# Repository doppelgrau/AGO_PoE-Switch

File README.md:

# AGO_PoE-Switch

A simple ethernet switch, four ports with passive PoE, one without.
Input protected against reverse polarity and over voltage (>15V)

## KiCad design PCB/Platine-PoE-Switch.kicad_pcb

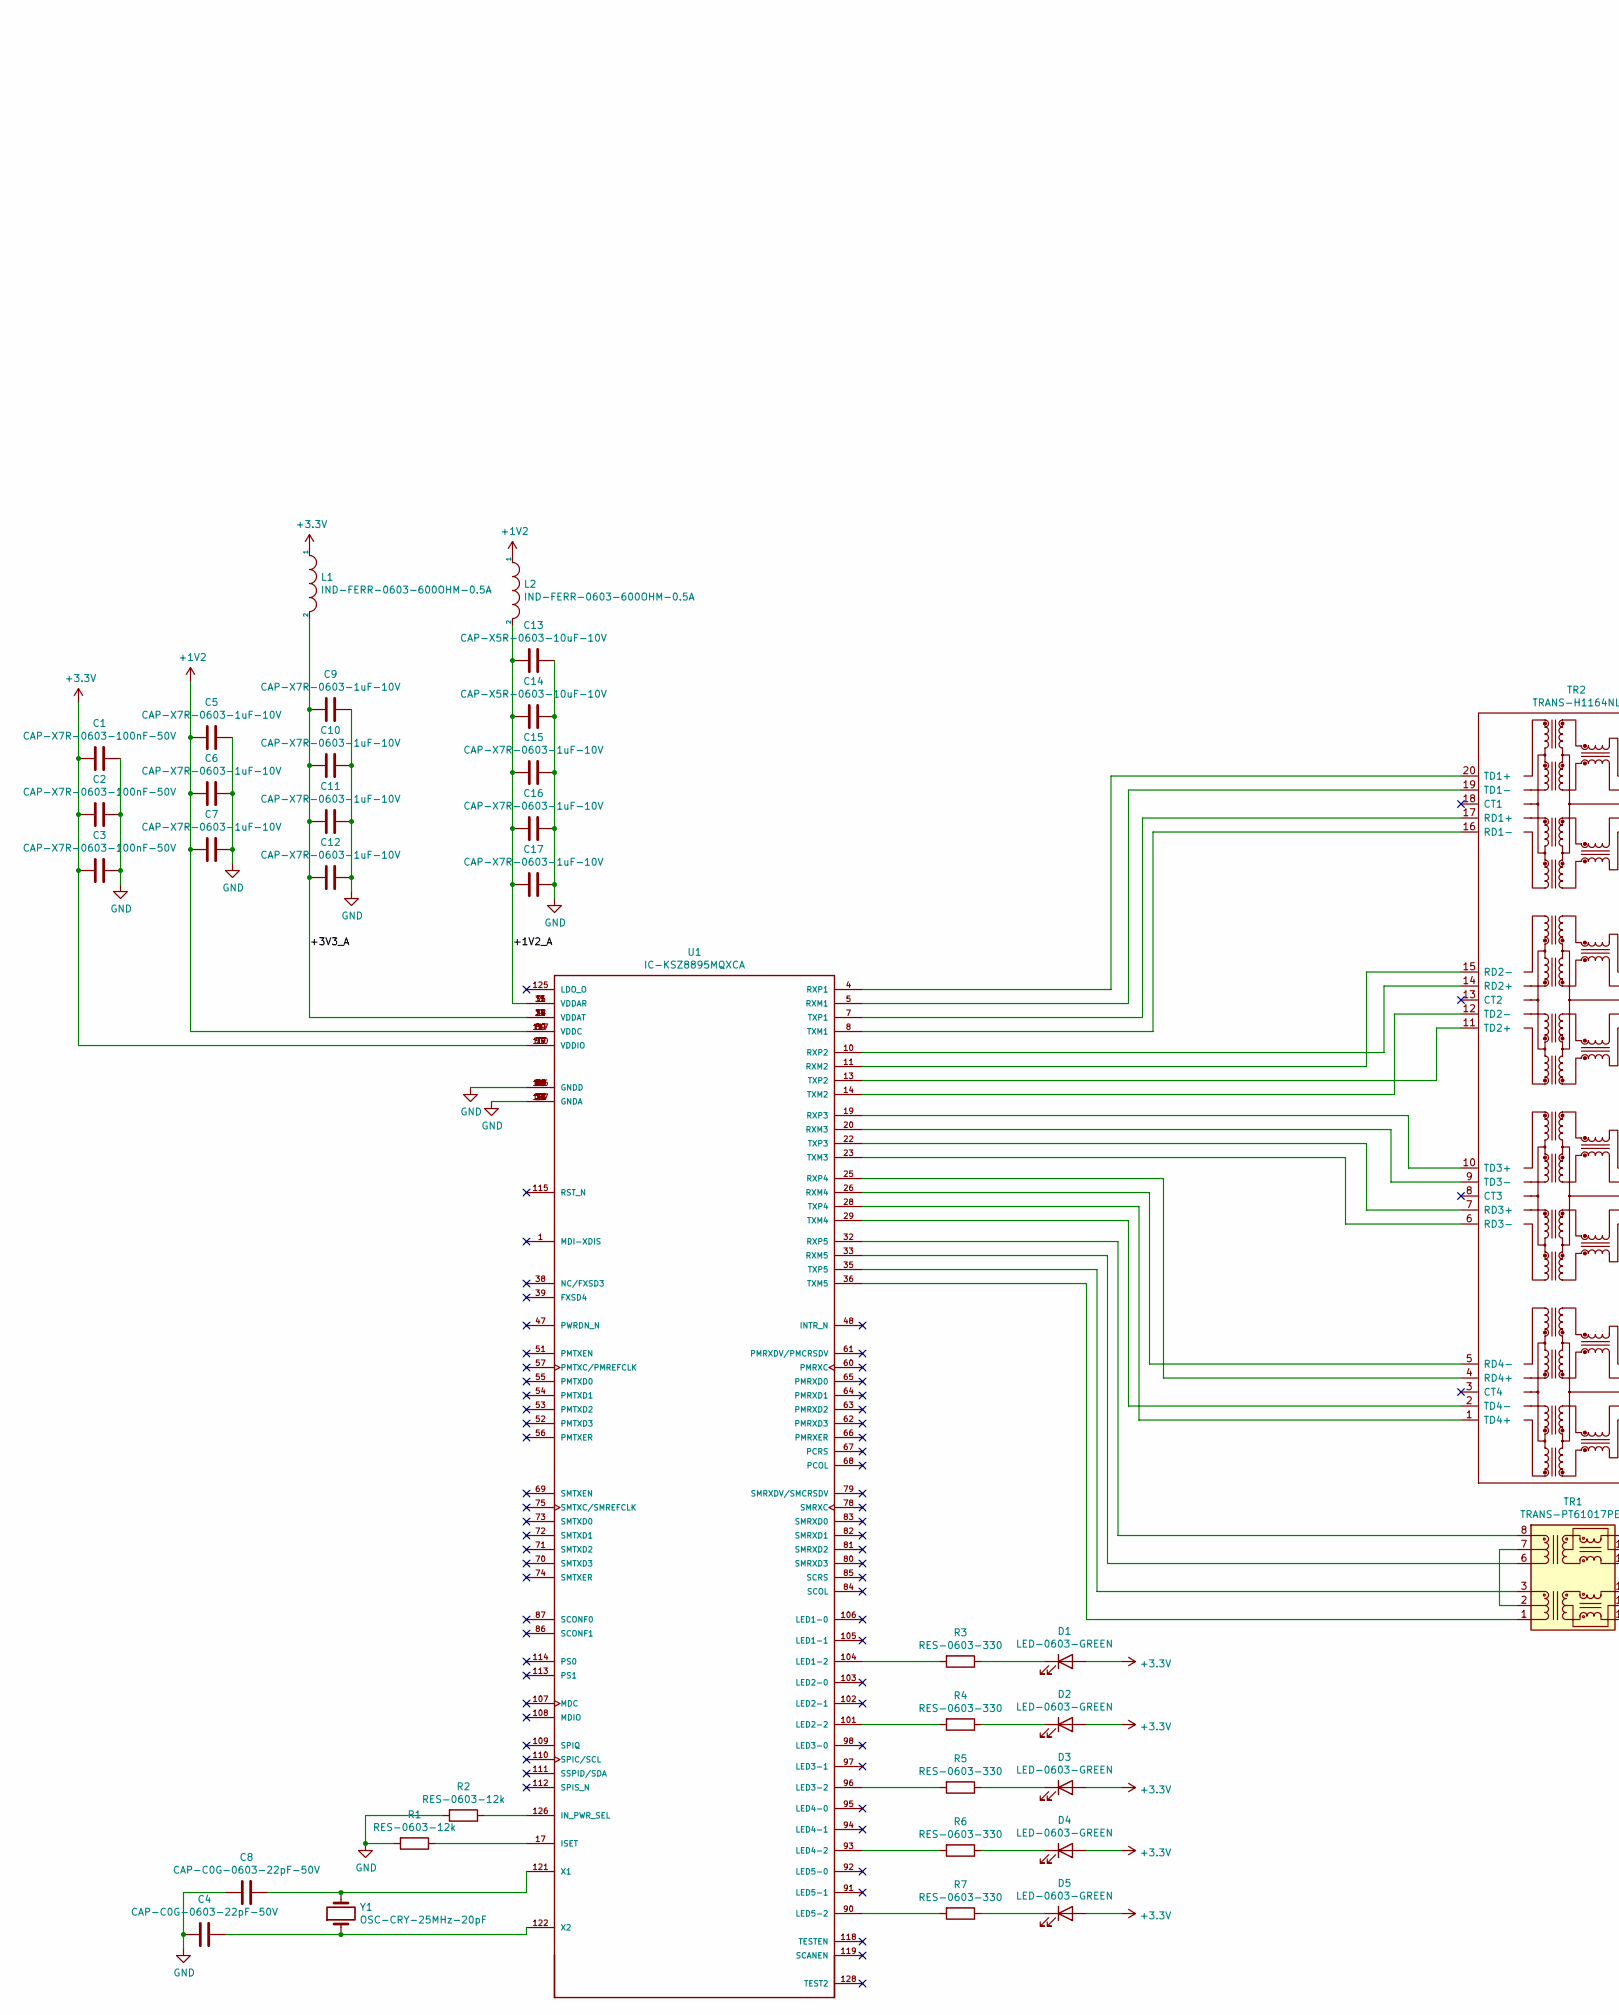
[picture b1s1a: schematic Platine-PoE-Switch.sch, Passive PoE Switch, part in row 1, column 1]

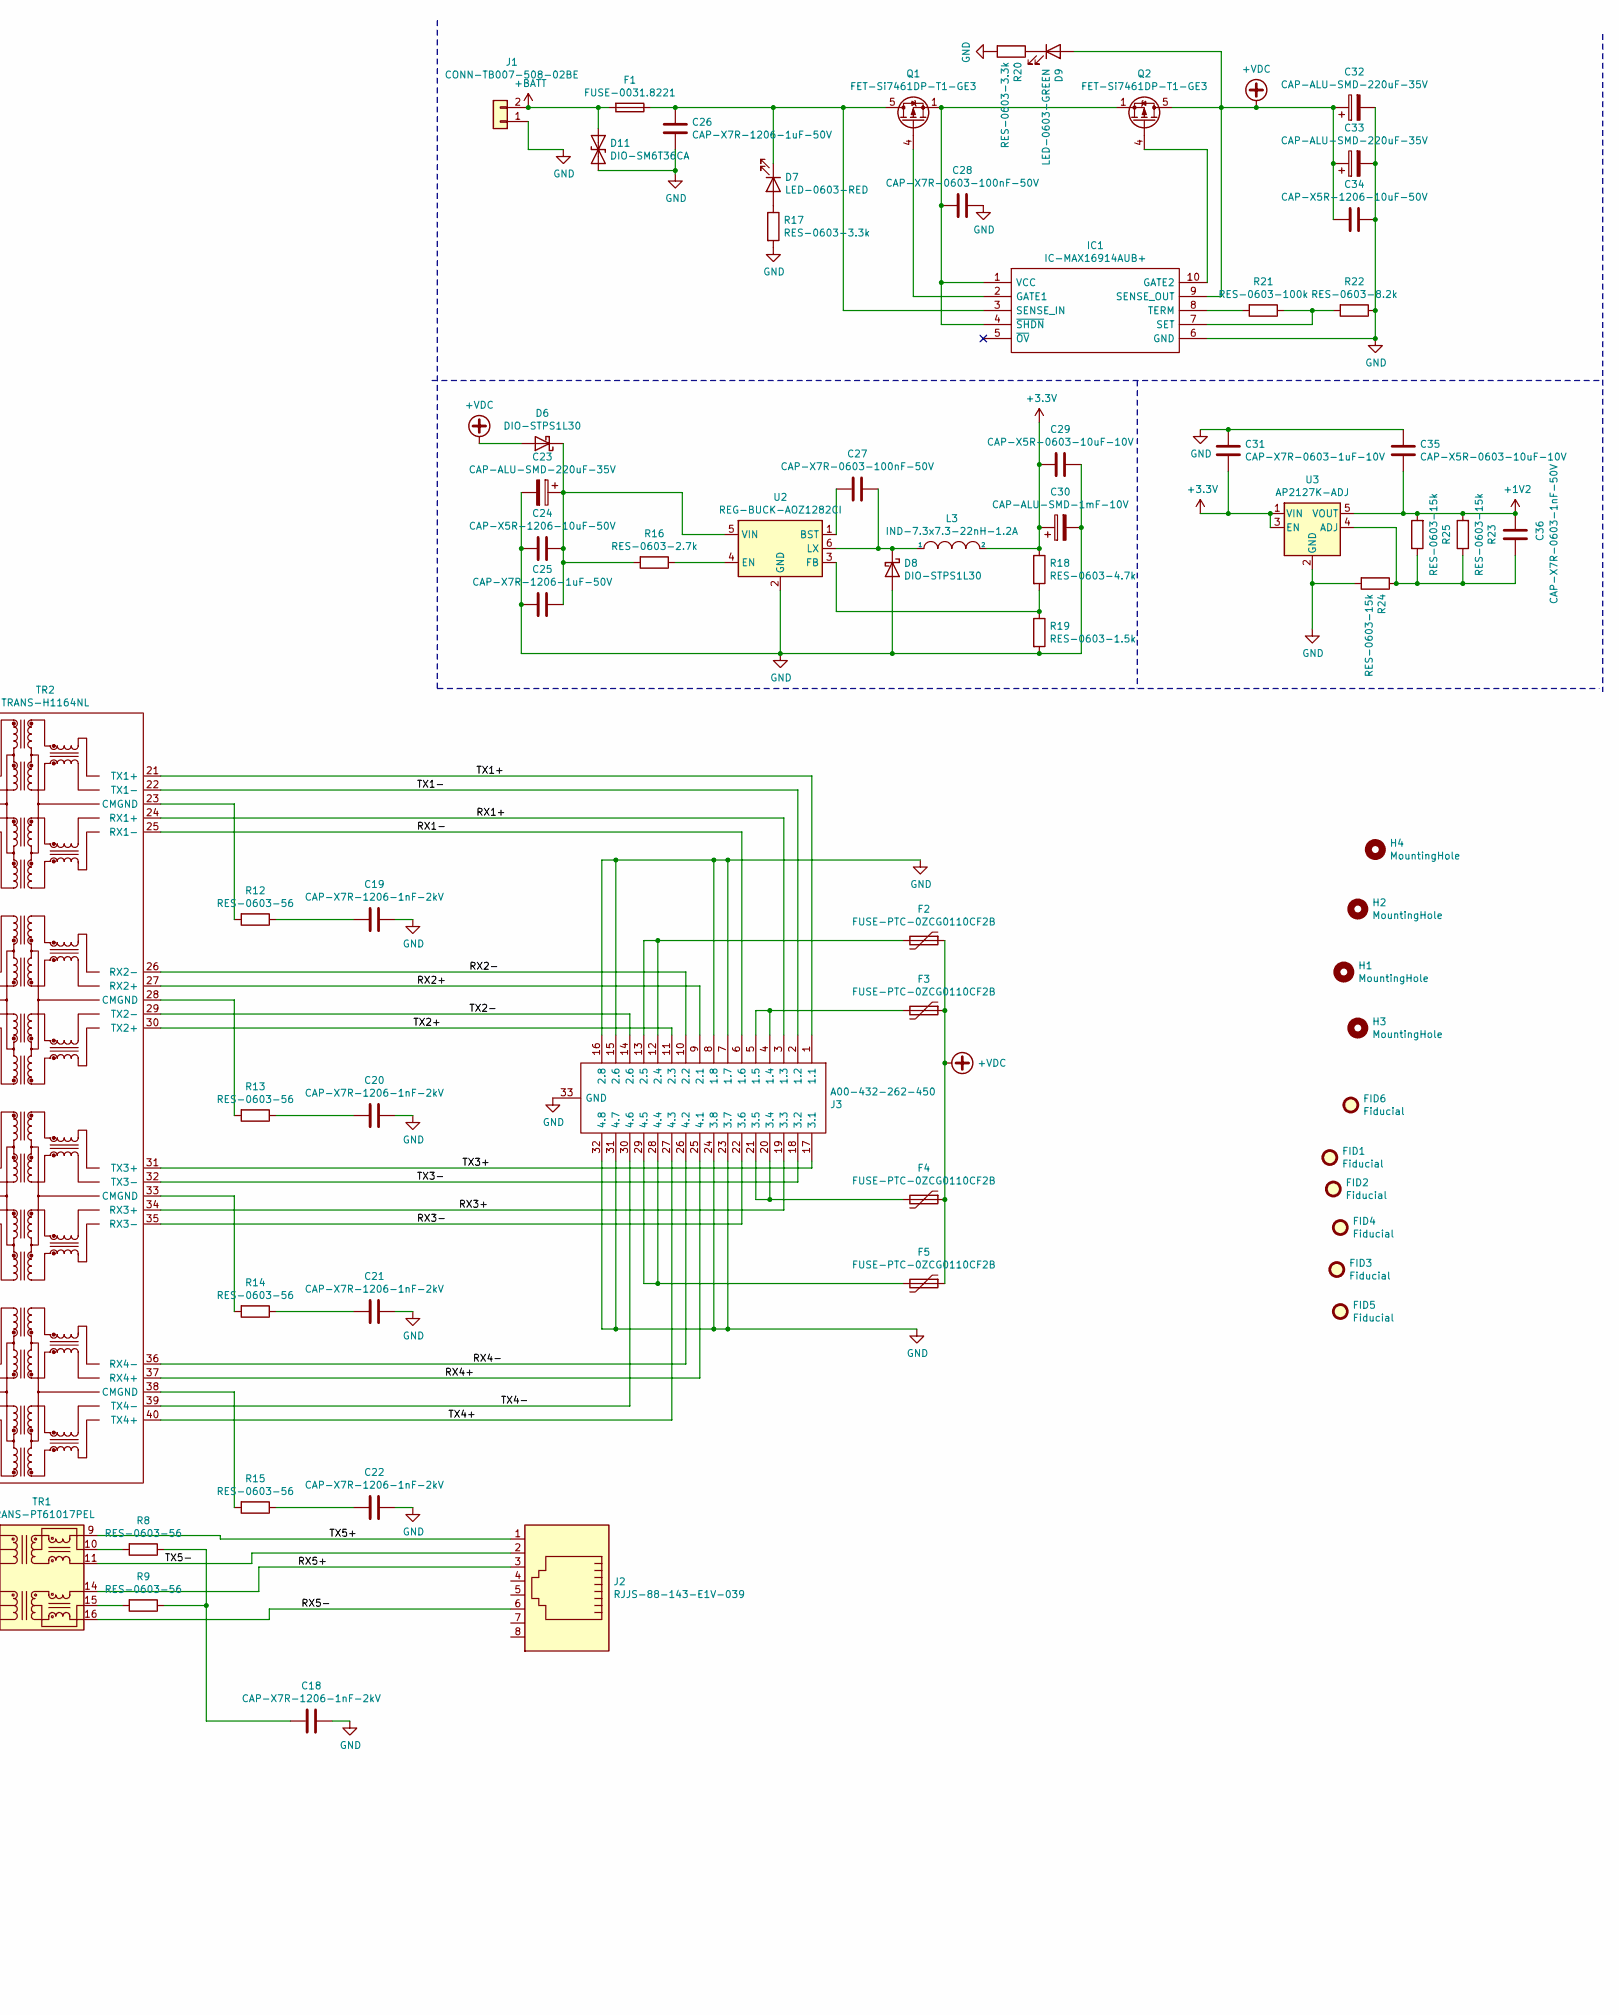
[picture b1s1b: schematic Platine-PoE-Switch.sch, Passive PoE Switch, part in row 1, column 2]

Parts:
C1, C2, C3, C27, C28: CAP-X7R-0603-100nF-50V; C_0603_1608Metric
C4, C8: CAP-C0G-0603-22pF-50V; C_0603_1608Metric
C5, C6, C7, C9, C10, C11, C12, C15, C16, C17, C31: CAP-X7R-0603-1uF-10V; C_0603_1608Metric
C13, C14, C29, C35: CAP-X5R-0603-10uF-10V; C_0603_1608Metric
C18, C19, C20, C21, C22: CAP-X7R-1206-1nF-2kV; C_1206_3216Metric
C23, C32, C33: CAP-ALU-SMD-220uF-35V; CP_Elec_10x10
C24, C34: CAP-X5R-1206-10uF-50V; C_1206_3216Metric
C25, C26: CAP-X7R-1206-1uF-50V; C_1206_3216Metric
C30: CAP-ALU-SMD-1mF-10V; CP_Elec_10x10
C36: CAP-X7R-0603-1nF-50V; C_0603_1608Metric
D1, D2, D3, D4, D5, D9: LED-0603-GREEN; LED_0603_1608Metric
D6, D8: DIO-STPS1L30; D_SMA
D7: LED-0603-RED; LED_0603_1608Metric
D11: DIO-SM6T36CA; D_SMB
F1: FUSE-0031.8221; Fuseholder_Cylinder-5x20mm_Schurter_SMD_0031.8221
F2, F3, F4, F5: FUSE-PTC-0ZCG0110CF2B; Fuse_1812_4532Metric
FID1, FID2, FID3, FID4, FID5, FID6: Fiducial; Fiducial_1mm_Mask2mm
H1, H2, H3, H4: MountingHole; MountingHole_3.2mm_M3
IC1: IC-MAX16914AUB+; SOP50P490X110-10N; Manufacturer_Part_Number MAX16914AUB+
J1: CONN-TB007-508-02BE; TerminalBlock_Phoenix_MKDS-1,5-2-5.08_1x02_P5.08mm_Horizont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
J2: RJJS-88-143-E1V-039
J3: A00-432-262-450; A00432262450; Mouser Part Number 587-A00-432-262-450
L1, L2: IND-FERR-0603-600OHM-0.5A; L_0603_1608Metric
L3: IND-7.3x7.3-22nH-1.2A; DE0703-22
Q1, Q2: FET-Si7461DP-T1-GE3; PowerPAK_SO-8_Single
R1, R2: RES-0603-12k; R_0603_1608Metric
R3, R4, R5, R6, R7: RES-0603-330; R_0603_1608Metric
R8, R9, R12, R13, R14, R15: RES-0603-56; R_0603_1608Metric
R16: RES-0603-2.7k; R_0603_1608Metric
R17, R20: RES-0603-3.3k; R_0603_1608Metric
R18: RES-0603-4.7k; R_0603_1608Metric
R19: RES-0603-1.5k; R_0603_1608Metric
R21: RES-0603-100k; R_0603_1608Metric
R22: RES-0603-8.2k; R_0603_1608Metric
R23, R24, R25: RES-0603-15k; R_0603_1608Metric
TR1: TRANS-PT61017PEL; Transformer_Ethernet_Bourns_PT61017PEL
TR2: TRANS-H1164NL; H1164NL
U1: IC-KSZ8895MQXCA; PQFP-128_14x20mm_P0.5mm
U2: REG-BUCK-AOZ1282CI; SOT-23-6
U3: AP2127K-ADJ; SOT-23-5
Y1: OSC-CRY-25MHz-20pF; Crystal_SMD_HC49-SD

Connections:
+1V2: C5.2, C6.2, C7.2, C35.2, C36.1, L2.1, R23.2, R25.2, U1.50 (VDDC), U1.89 (VDDC), U1.117 (VDDC), U3.5 (VOUT)
+3V3: C1.2, C2.2, C3.2, C29.2, C30.1, C31.2, D1.2 (A), D2.2 (A), D3.2 (A), D4.2 (A), D5.2 (A), L1.1, L3.2, R18.1, U1.59 (VDDIO), U1.77 (VDDIO), U1.100 (VDDIO), U3.1 (VIN), U3.3 (EN)
+BATT: D11.1 (A1), F1.2, J1.2
+VDC: C32.1, C33.1, C34.1, D6.2 (A), D9.2 (A), F2.1, F3.1, F4.1, F5.1, IC1.9 (SENSE_OUT), Q2.5 (D)
/+1V2_A: C13.2, C14.2, C15.2, C16.2, C17.2, L2.2, U1.3 (VDDAR), U1.15 (VDDAR), U1.31 (VDDAR)
/+3V3_A: C9.2, C10.2, C11.2, C12.2, L1.2, U1.9 (VDDAT), U1.18 (VDDAT), U1.24 (VDDAT), U1.37 (VDDAT)
/RX1+: J3.3 (1.3), TR2.24 (RX1+)
/RX1-: J3.6 (1.6), TR2.25 (RX1-)
/RX2+: J3.9 (2.1), TR2.27 (RX2+)
/RX2-: J3.10 (2.2), TR2.26 (RX2-)
/RX3+: J3.19 (3.3), TR2.34 (RX3+)
/RX3-: J3.22 (3.6), TR2.35 (RX3-)
/RX4+: J3.25 (4.1), TR2.37 (RX4+)
/RX4-: J3.26 (4.2), TR2.36 (RX4-)
/RX5+: J2.3, TR1.14 (TX-)
/RX5-: J2.6, TR1.16 (TX+)
/TX1+: J3.1 (1.1), TR2.21 (TX1+)
/TX1-: J3.2 (1.2), TR2.22 (TX1-)
/TX2+: J3.11 (2.3), TR2.30 (TX2+)
/TX2-: J3.14 (2.6), TR2.29 (TX2-)
/TX3+: J3.17 (3.1), TR2.31 (TX3+)
/TX3-: J3.18 (3.2), TR2.32 (TX3-)
/TX4+: J3.27 (4.3), TR2.40 (TX4+)
/TX4-: J3.30 (4.6), TR2.39 (TX4-)
/TX5+: J2.1, TR1.9 (RX-)
/TX5-: J2.2, TR1.11 (RX+)
GND: C1.1, C2.1, C3.1, C4.2, C5.1, C6.1, C7.1, C8.2, C9.1, C10.1, C11.1, C12.1, C13.1, C14.1, C15.1, C16.1, C17.1, C18.1, C19.1, C20.1, C21.1, C22.1, C23.2, C24.2, C25.2, C26.2, C28.1, C29.1, C30.2, C31.1, C32.2, C33.2, C34.2, C35.1, D8.2 (A), D11.2 (A2), IC1.6 (GND), J1.1, J3.7 (1.7), J3.8 (1.8), J3.15 (2.6), J3.16 (2.8), J3.23 (3.7), J3.24 (3.8), J3.31 (4.7), J3.32 (4.8), J3.33 (GND), J3.34, J3.35, J3.36, J3.37, R1.2, R2.2, R17.2, R19.2, R20.2, R22.1, R24.2, U1.2 (GNDA), U1.6 (GNDA), U1.12 (GNDA), U1.16 (GNDA), U1.21 (GNDA), U1.27 (GNDA), U1.30 (GNDA), U1.34 (GNDA), U1.49 (GNDD), U1.58 (GNDD), U1.76 (GNDD), U1.88 (GNDD), U1.99 (GNDD), U1.116 (GNDD), U1.127 (GNDA), U2.2 (GND), U3.2 (GND)
unnamed: C4.1, U1.122 (X2), Y1.1
unnamed: C8.1, U1.121 (X1), Y1.2
unnamed: C18.2, R8.1, R9.1
unnamed: C19.2, R12.1
unnamed: C20.2, R13.1
unnamed: C21.2, R14.1
unnamed: C22.2, R15.1
unnamed: C23.1, C24.1, C25.1, D6.1 (K), R16.2, U2.5 (VIN)
unnamed: C26.1, D7.1 (K), F1.1, IC1.3 (SENSE_IN), Q1.5 (D)
unnamed: C27.1, D8.1 (K), L3.1, U2.6 (LX)
unnamed: C27.2, U2.1 (BST)
unnamed: C28.2, IC1.1 (VCC), IC1.4 (~SHDN), Q1.1 (S), Q1.2 (S), Q1.3 (S), Q2.1 (S), Q2.2 (S), Q2.3 (S)
unnamed: C36.2, R23.1, R24.1, R25.1, U3.4 (ADJ)
unnamed: D1.1 (K), R3.1
unnamed: D2.1 (K), R4.1
unnamed: D3.1 (K), R5.1
unnamed: D4.1 (K), R6.1
unnamed: D5.1 (K), R7.1
unnamed: D7.2 (A), R17.1
unnamed: D9.1 (K), R20.1
unnamed: F2.2, J3.12 (2.4), J3.13 (2.5)
unnamed: F3.2, J3.4 (1.4), J3.5 (1.5)
unnamed: F4.2, J3.20 (3.4), J3.21 (3.5)
unnamed: F5.2, J3.28 (4.4), J3.29 (4.5)
unnamed: IC1.2 (GATE1), Q1.4 (G)
unnamed: IC1.7 (SET), R21.1, R22.2
unnamed: IC1.8 (TERM), R21.2
unnamed: IC1.10 (GATE2), Q2.4 (G)
unnamed: R1.1, U1.17 (ISET)
unnamed: R2.1, U1.126 (IN_PWR_SEL)
unnamed: R3.2, U1.104 (LED1-2)
unnamed: R4.2, U1.101 (LED2-2)
unnamed: R5.2, U1.96 (LED3-2)
unnamed: R6.2, U1.93 (LED4-2)
unnamed: R7.2, U1.90 (LED5-2)
unnamed: R8.2, TR1.10 (C_RX)
unnamed: R9.2, TR1.15 (C_TX)
unnamed: R12.2, TR2.23 (CMGND)
unnamed: R13.2, TR2.28 (CMGND)
unnamed: R14.2, TR2.33 (CMGND)
unnamed: R15.2, TR2.38 (CMGND)
unnamed: R16.1, U2.4 (EN)
unnamed: R18.2, R19.1, U2.3 (FB)
unnamed: TR1.1 (TD+), U1.36 (TXM5)
unnamed: TR1.2 (C_TD), TR1.7 (C_RD)
unnamed: TR1.3 (TD-), U1.35 (TXP5)
unnamed: TR1.6 (RD+), U1.33 (RXM5)
unnamed: TR1.8 (RD-), U1.32 (RXP5)
unnamed: TR2.1 (TD4+), U1.28 (TXP4)
unnamed: TR2.2 (TD4-), U1.29 (TXM4)
unnamed: TR2.4 (RD4+), U1.25 (RXP4)
unnamed: TR2.5 (RD4-), U1.26 (RXM4)
unnamed: TR2.6 (RD3-), U1.23 (TXM3)
unnamed: TR2.7 (RD3+), U1.22 (TXP3)
unnamed: TR2.9 (TD3-), U1.20 (RXM3)
unnamed: TR2.10 (TD3+), U1.19 (RXP3)
unnamed: TR2.11 (TD2+), U1.13 (TXP2)
unnamed: TR2.12 (TD2-), U1.14 (TXM2)
unnamed: TR2.14 (RD2+), U1.10 (RXP2)
unnamed: TR2.15 (RD2-), U1.11 (RXM2)
unnamed: TR2.16 (RD1-), U1.8 (TXM1)
unnamed: TR2.17 (RD1+), U1.7 (TXP1)
unnamed: TR2.19 (TD1-), U1.5 (RXM1)
unnamed: TR2.20 (TD1+), U1.4 (RXP1)

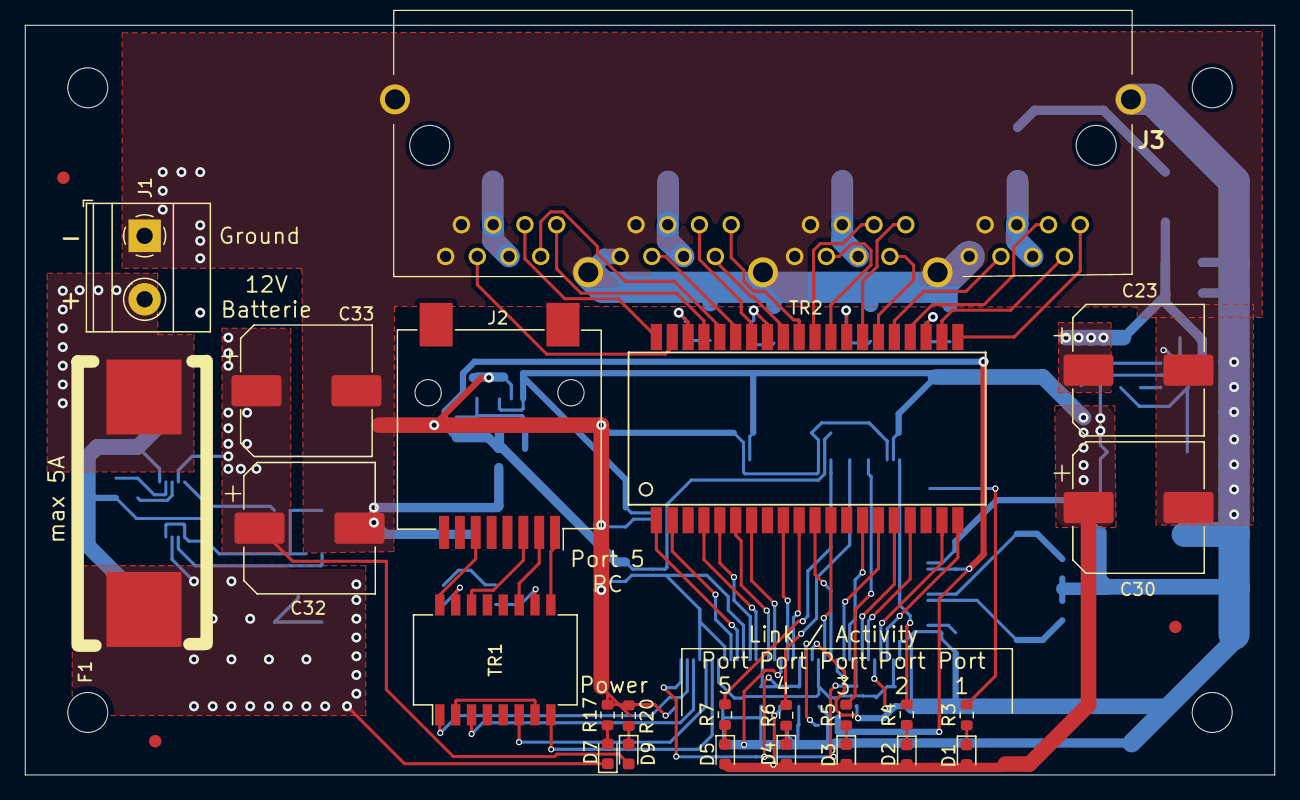
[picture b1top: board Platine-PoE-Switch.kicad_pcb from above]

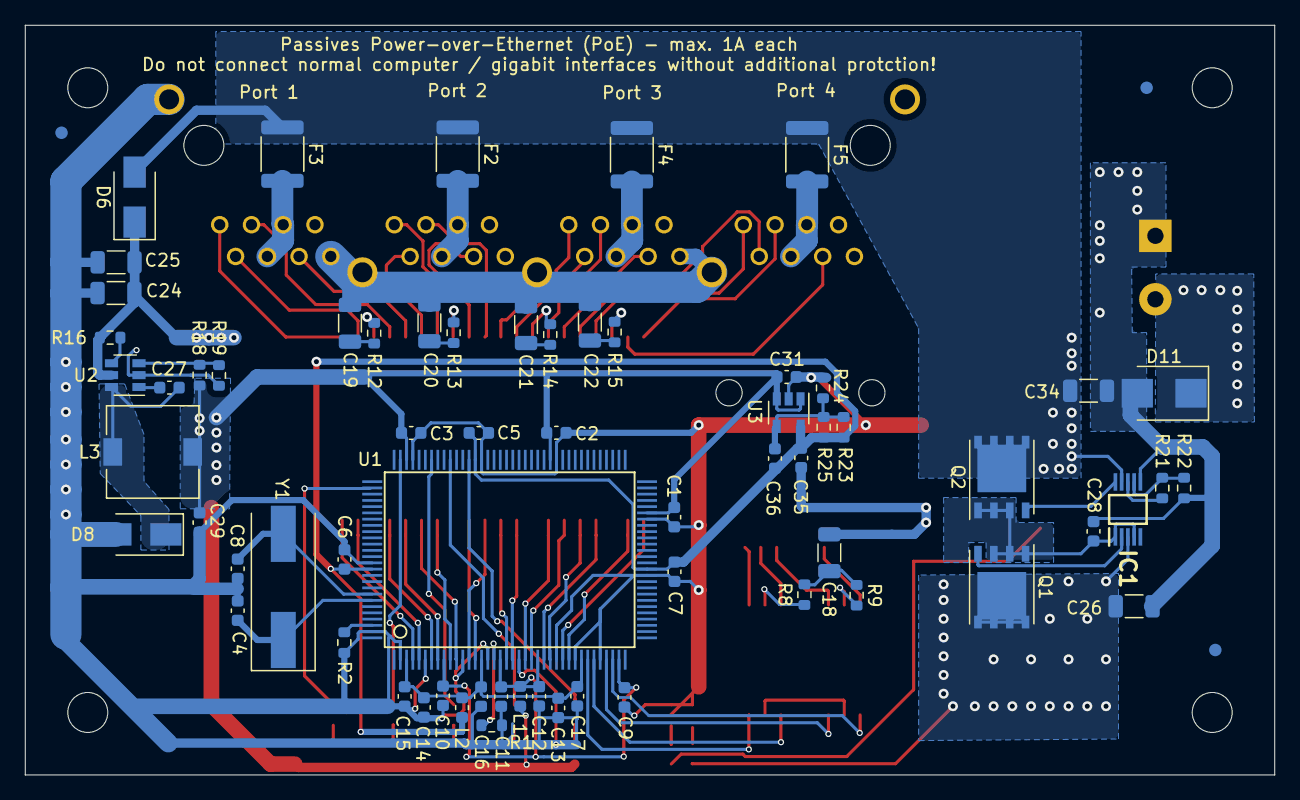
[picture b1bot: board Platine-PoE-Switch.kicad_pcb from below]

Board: 2 copper layers, 100.0 x 60.0 mm, 99 parts (68 on the bottom side), 91 nets.

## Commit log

2021-09-09 Import
2021-09-09 added PDF
